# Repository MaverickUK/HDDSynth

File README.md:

# HDD Synth
<div style="background: white; display: inline-block; padding: 8px;">
  
</div>

### Recreates the sound of mechanical spinning HDDs on retro PCs that use a solid state drive.

Inspired by seeing the HDD Clicker project and wanting to more faithfully recreate the sound of old mechanical hard drives spinning up and accessing data. Because the hard drive sounds come from samples, it's possible to replace them with any hard drive recording you'd like or something completely different!

## Features

- **Sample based recreation** of mechanical hard disk drives operating sounds
 - **Spin up** when PC is turned on
 - **Idle hum** whilst standing by
 - **Access** clicks and crackcles
 - **Spin down** when PC is turned off
- **SD card** to hold multiple HDD sample packs, to recreate the sound of different mechanical hard disk drives
- **Volume control** to make it very loud or silent
- **Balance** to alter the amount of idle to access sounds
- **HDD detection** via HDD LED
- **HDD LED** to connect to your case
- **OLED screen** to view activity, volume and more

## Progress
### Beta test is active
The MKV prototype boards are with a small group of beta testers to shake out any last issues before the boards are made available for sale.

It's been a long road, but the end is in sight

## Media
[View gallery](media.md)

<!--
## Usage

## License
-->

## Contact
Peter Bridger at [maverickuk@gmail.com](maverickuk@gmail.com)

Project website at [www.strifestreams.com/hddsynth](https://www.strifestreams.com/hddsynth)

## Resources
- [ISA System Architecture by Tom Shanley](https://archive.org/details/ISA_System_Architecture)
- [Intel ISA Bus Specification](https://archive.org/details/bitsavers_intelbusSpep89_3342148)
- [ISA bus technical summary](http://wearcam.org/ece385/lecture6/isa.htm)

## Acknowledgments
- Inspired by the [HDD Clicker project](https://www.serdashop.com/HDDClicker)
- A big thanks to [Ian Scott of PicoGUS fame](https://picog.us/) for sharing his resource sources and knowledge of using the Pi Pico with the ISA bus which gave me the confidence to take this project to the next level
- [Marten Electric](https://www.martenelectric.cz/) for the excellent ISA prototyping boards which made it very easy to wire up the Pico to my computer

### PCBWay
Thanks to [PCBWay](https://www.pcbway.com) for their PCB manufacturing and assembly services. This is my first PCB based project and they've been a great way to get quality PCB prototypes created along with component assembly at competitive prices. Recommended if you're thinking about creating a simular project yourself.

## License
This project is dual-licensed:

- **Software/firmware** is licensed under the [GNU GPL v3.0](LICENSE-CODE).
- **Hardware designs** (schematics, PCB files, BOM) are licensed under
  [CC BY-NC-SA 4.0](LICENSE-HARDWARE) — free for personal, non-commercial
  use and modification, but commercial use requires my permission.

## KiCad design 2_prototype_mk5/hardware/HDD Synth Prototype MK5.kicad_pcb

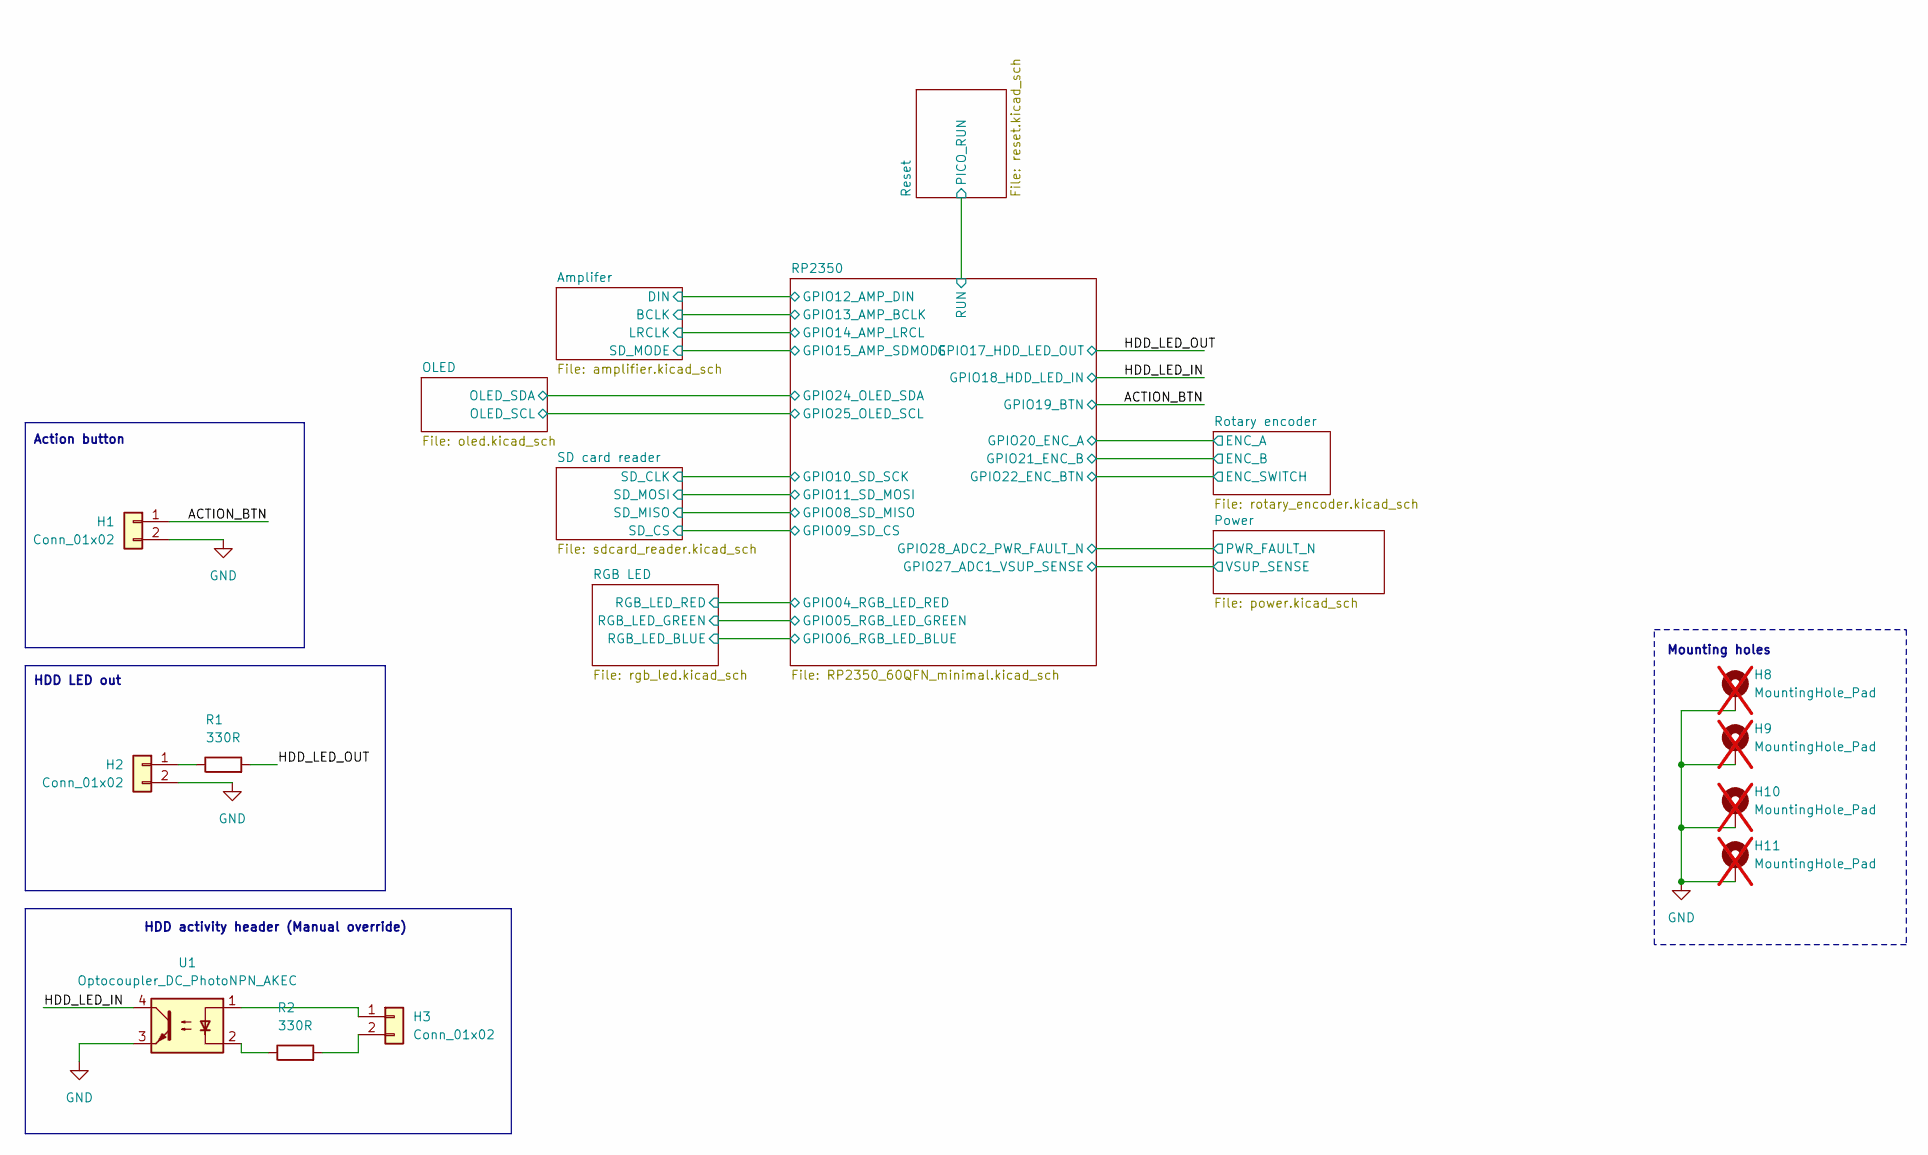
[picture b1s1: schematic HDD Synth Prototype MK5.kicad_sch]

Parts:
H1, H2, H3: Conn_01x02; PinHeader_1x02_P2.54mm_Vertical; LCSC Part Number C124375
H8, H9, H10, H11: MountingHole_Pad; MountingHole_3.2mm_M3_Pad; not fitted
R1, R2: 330R; R_0603_1608Metric; Manufacturer_Part_Number RC0603FR-07330RL; LCSC Part Number C23138
U1: Optocoupler_DC_PhotoNPN_AKEC; SO-4_4.4x3.6mm_P2.54mm; Manufacturer_Part_Number EL357N(C)(TA)-VG; LCSC Part Number C42381015

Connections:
/ACTION_BTN: H1.1; also elsewhere on the board
/HDD_LED_IN: U1.4; also elsewhere on the board
/HDD_LED_OUT: R1.2; also elsewhere on the board
GND: H1.2, H2.2, H8.1 (1_1), H9.1 (1_1), H10.1 (1_1), H11.1 (1_1), U1.3; also elsewhere on the board
unnamed: H2.1, R1.1
unnamed: H3.1, U1.1
unnamed: H3.2, R2.2
unnamed: R2.1, U1.2

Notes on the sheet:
Action button
Mounting holes
HDD activity header (Manual override)
HDD LED out

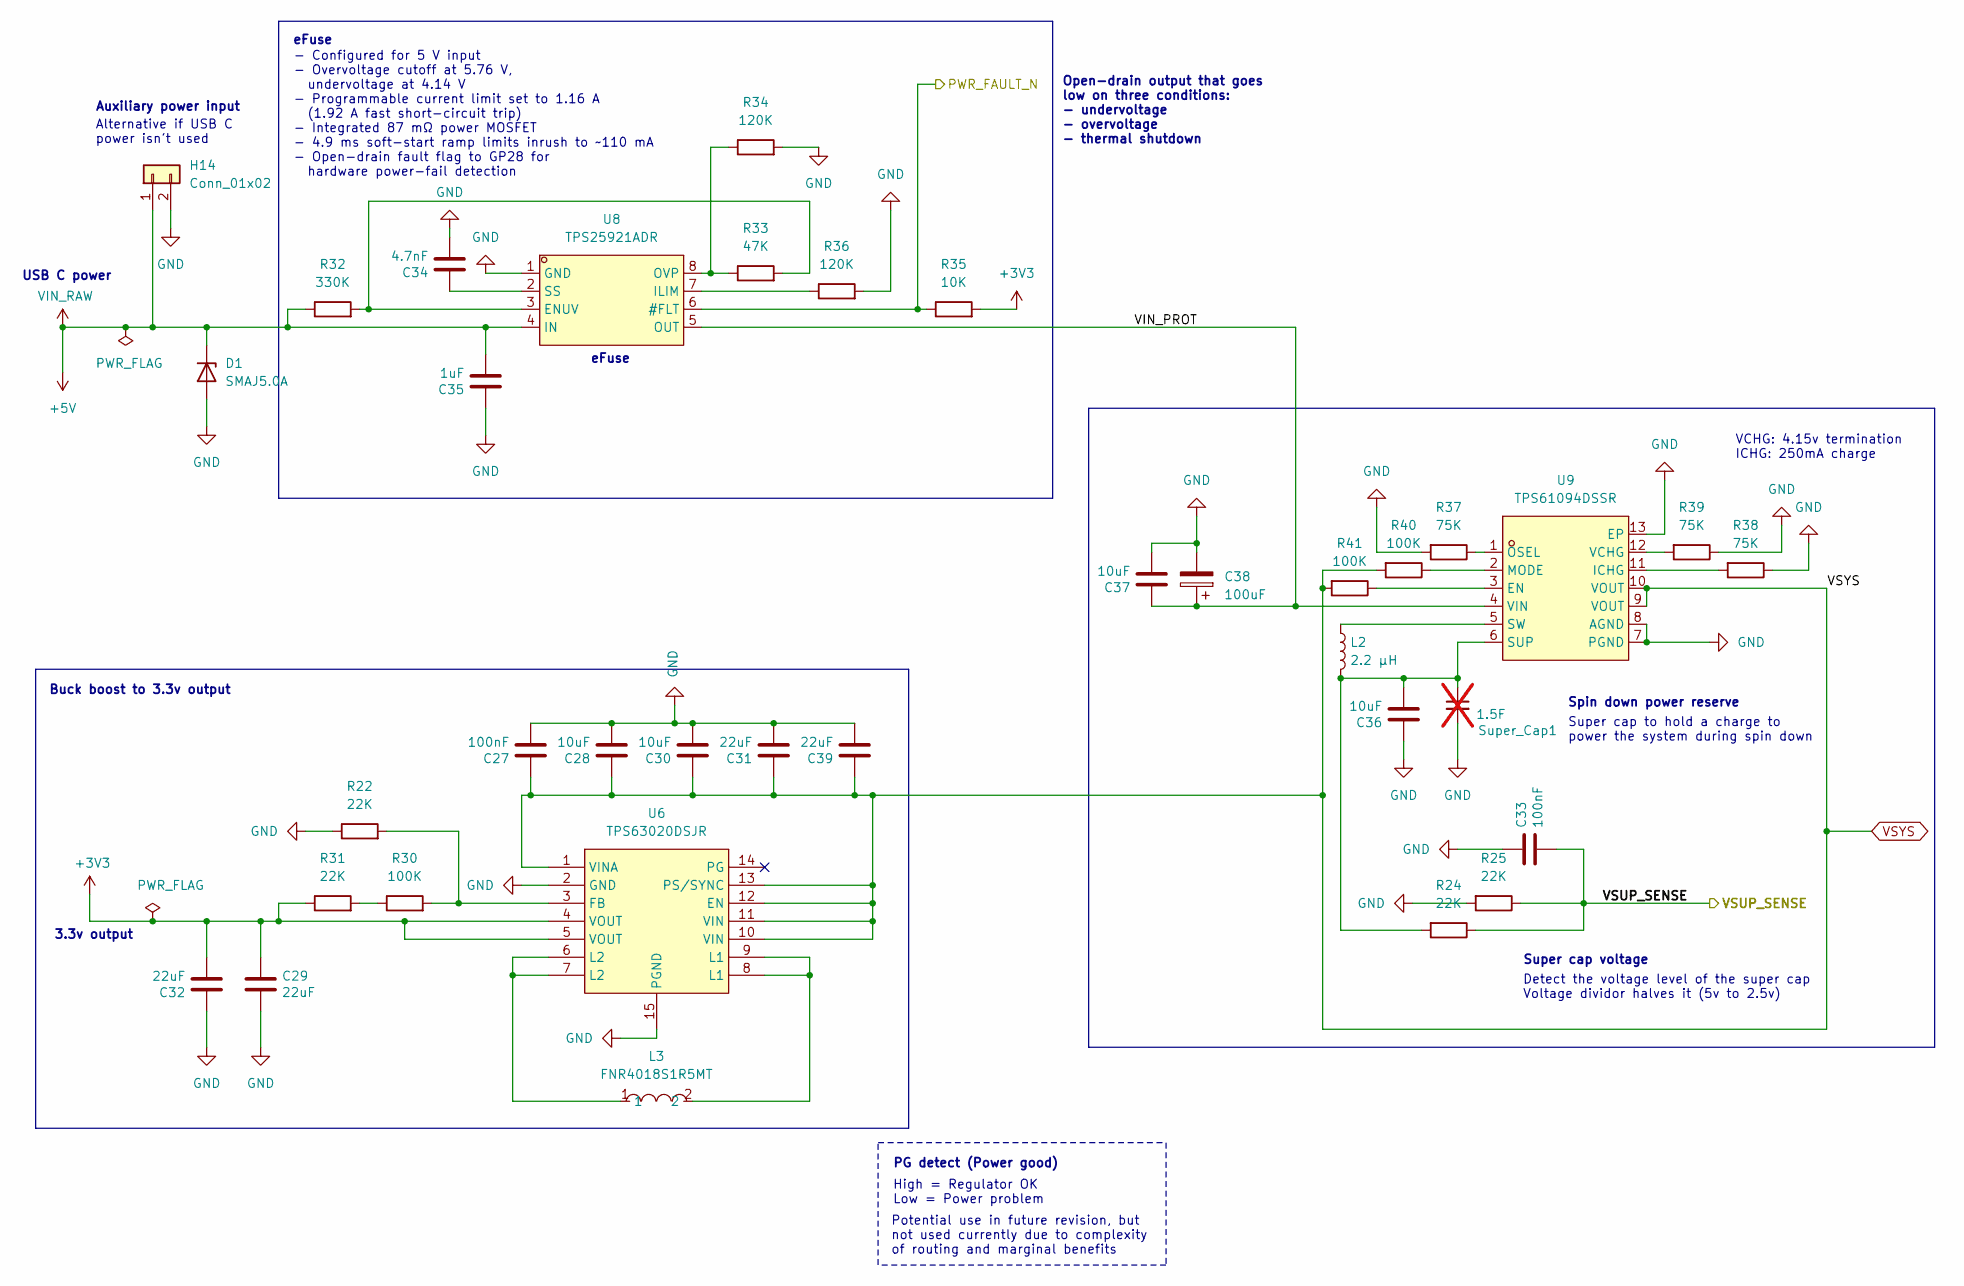
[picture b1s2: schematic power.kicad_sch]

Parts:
C27, C33: 100nF; C_0402_1005Metric; LCSC Part Number C1525
C28, C30, C36, C37: 10uF; C_0805_2012Metric; LCSC Part Number C15850
C29, C31, C32, C39: 22uF; C_0805_2012Metric; LCSC Part Number C45783
C34: 4.7nF; C_0402_1005Metric
C35: 1uF; C_0402_1005Metric
C38: 100uF; CP_Elec_6.3x7.7; LCSC Part Number C134801
D1: SMAJ5.0A; D_SMA
H14: Conn_01x02; PinHeader_1x02_P2.54mm_Vertical; LCSC Part Number C124375
L2: 2.2 µH; IND-SMD_L4.0-W4.0_FNR40XXS; LCSC Part Number C167804
L3: FNR4018S1R5MT; IND-SMD_L4.0-W4.0_FNR40XXS; MPN FNR4018S1R5MT; LCSC Part Number C167802
R22, R31: 22K; R_0402_1005Metric; LCSC Part Number C25768
R24, R25: 22K; R_0603_1608Metric; Manufacturer_Part_Number RC0603FR-071KL; LCSC Part Number C31850
R30, R40, R41: 100K; R_0402_1005Metric; LCSC Part Number C25741
R32: 330K; R_0402_1005Metric; LCSC Part Number C25778
R33: 47K; R_0402_1005Metric; LCSC Part Number C25792
R34, R36: 120K; R_0402_1005Metric; LCSC Part Number C25750
R35: 10K; R_0402_1005Metric; LCSC Part Number C25744
R37, R38, R39: 75K; R_0402_1005Metric; LCSC Part Number C25798
Super_Cap1: 1.5F; SuperCap_Eaton_PHV_9.0x17.3mm_P11.80mm; not fitted
U6: TPS63020DSJR; VSON-14_L4.0-W3.0-P0.50-BL-EP_TI_DSJ; MPN TPS63020DSJR; LCSC Part Number C15483
U8: TPS25921ADR; SOIC-8_L5.0-W4.0-P1.27-LS6.0-BL; MPN TPS25921ADR; LCSC Part Number C189199
U9: TPS61094DSSR; WSON-12_L3.0-W2.0-P0.5-BL-EP; MPN TPS61094DSSR; LCSC Part Number C3034939

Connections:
+3V3: C29.1, C32.2, R31.1, R35.2, U6.4 (VOUT), U6.5 (VOUT); also elsewhere on the board
+5V: C35.2, D1.1 (K), H14.1, R32.1, U8.4 (IN); also elsewhere on the board
/Power/VIN_PROT: C37.1, C38.1, U8.5 (OUT), U9.4 (VIN)
/Power/VSUP_SENSE: C33.2, R24.1, R25.1; also elsewhere on the board
/RP2350/PWR_FAULT_N: R35.1, U8.6 (#FLT); also elsewhere on the board
GND: C27.2, C28.2, C29.2, C30.2, C31.2, C32.1, C33.1, C34.2, C35.1, C36.1, C37.2, C38.2, C39.2, D1.2 (A), H14.2, R22.1, R25.2, R34.2, R36.2, R37.2, R38.1, R39.1, Super_Cap1.2, U6.2 (GND), U6.15 (PGND), U8.1 (GND), U9.7 (PGND), U9.8 (AGND), U9.13 (EP); also elsewhere on the board
unnamed: L3.1, U6.6 (L2), U6.7 (L2)
unnamed: L3.2, U6.8 (L1), U6.9 (L1)
unnamed: R30.1, R31.2
unnamed: R22.2, R30.2, U6.3 (FB)
unnamed: R32.2, R33.2, U8.3 (ENUV)
unnamed: R36.1, U8.7 (ILIM)
unnamed: R33.1, R34.1, U8.8 (OVP)
unnamed: C34.1, U8.2 (SS)
unnamed: R41.1, U9.3 (EN)
unnamed: R38.2, U9.11 (ICHG)
unnamed: R40.1, U9.2 (MODE)
unnamed: R37.1, U9.1 (OSEL)
unnamed: C36.2, L2.2, R24.2, Super_Cap1.1, U9.6 (SUP)
unnamed: L2.1, U9.5 (SW)
unnamed: R39.2, U9.12 (VCHG)
VSYS: C27.1, C28.1, C30.1, C31.1, C39.1, R40.2, R41.2, U6.1 (VINA), U6.10 (VIN), U6.11 (VIN), U6.12 (EN), U6.13 (PS/SYNC), U9.9 (VOUT), U9.10 (VOUT); also elsewhere on the board

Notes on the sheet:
Potential use in future revision, but not used currently due to complexity of routing and marginal benefits
- Configured for 5 V input - Overvoltage cutoff at 5.76 V, undervoltage at 4.14 V - Programmable current limit set to 1.16 A (1.92 A fast short-circuit trip) - Integrated 87 mΩ power MOSFET - 4.9 ms soft-start ramp limits inrush to ~110 mA - Open-drain fault flag to GP28 for hardware power-fail det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
Alternative if USB C power isn't used
VCHG: 4.15v termination ICHG: 250mA charge
Super cap to hold a charge to power the system during spin down
eFuse
3.3v output
Open-drain output that goes low on three conditions: - undervoltage - overvoltage - thermal shutdown
Super cap voltage
PG detect (Power good)
Buck boost to 3.3v output
Spin down power reserve
High = Regulator OK Low = Power problem
USB C power
Detect the voltage level of the super cap Voltage dividor halves it (5v to 2.5v)
Auxiliary power input

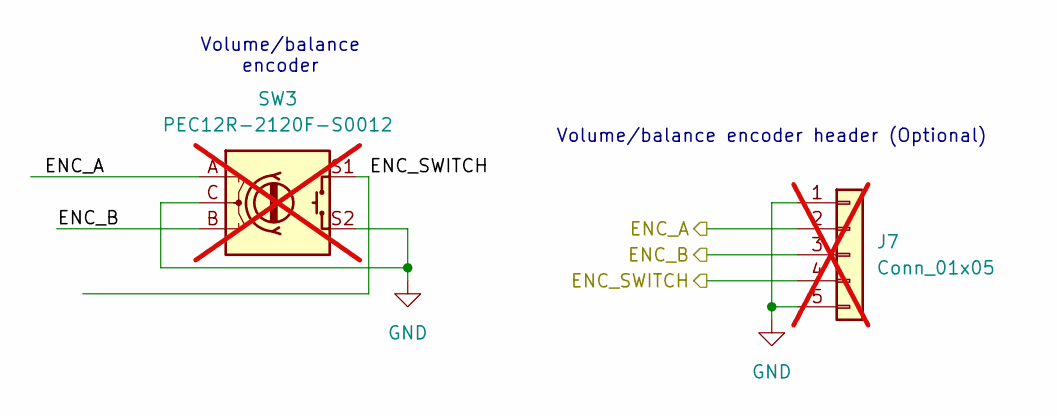
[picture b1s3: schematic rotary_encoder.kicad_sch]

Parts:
J7: Conn_01x05; PinHeader_1x05_P2.54mm_Vertical; LCSC Part Number C124379; not fitted
SW3: PEC12R-2120F-S0012; RotaryEncoder_Bourns_Horizontal_PEC12R-2x17F-Sxxxx; Manufacturer_Part_Number PEC12R-2120F-S0012; not fitted

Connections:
/RP2350/ENC_A: J7.2; also elsewhere on the board
/RP2350/ENC_B: J7.3; also elsewhere on the board
/RP2350/ENC_BTN: J7.4; also elsewhere on the board
GND: J7.1, J7.5, SW3.C, SW3.S2; also elsewhere on the board

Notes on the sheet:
Volume/balance encoder
Volume/balance encoder header (Optional)

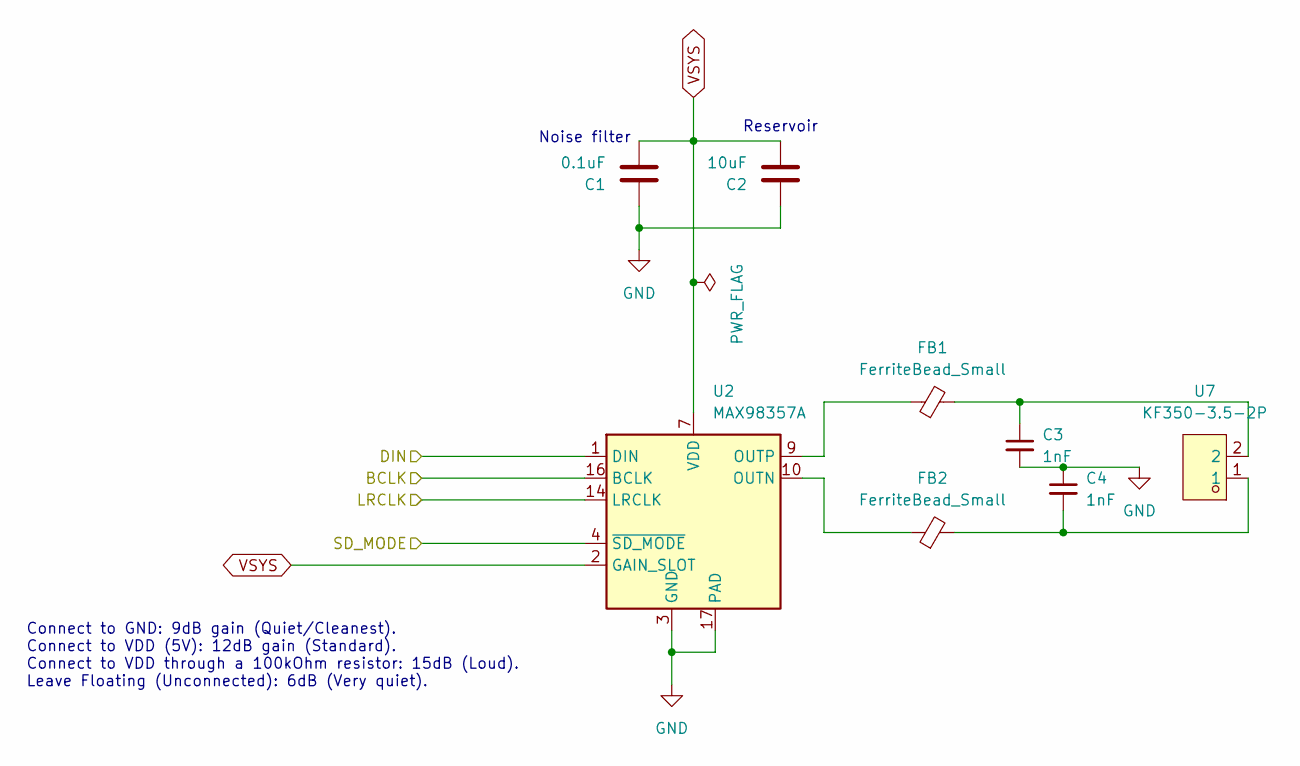
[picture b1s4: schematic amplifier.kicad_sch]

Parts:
C1: 0.1uF; C_0603_1608Metric; Manufacturer_Part_Number CL10B104KO8NNNC; LCSC Part Number C14663
C2: 10uF; C_1206_3216Metric; Manufacturer_Part_Number CL31A106KAHNNNE; LCSC Part Number C13585
C3, C4: 1nF; C_0603_1608Metric; Manufacturer_Part_Number 0603B102K500NT; LCSC Part Number C1588
FB1, FB2: FerriteBead_Small; L_0805_2012Metric; Manufacturer_Part_Number BLM21PG221SN1D; LCSC Part Number C85840
U2: MAX98357A; TQFN-16-1EP_3x3mm_P0.5mm_EP1.23x1.23mm; Manufacturer_Part_Number MAX98357AETE+T; LCSC Part Number C910544
U7: KF350-3.5-2P; CONN-TH_P3.50_KF350-3.5-2P; MPN KF350-3.5-2P; LCSC Part Number C474892

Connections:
/RP2350/AMP_BCLK: U2.16 (BCLK); also elsewhere on the board
/RP2350/AMP_DIN: U2.1 (DIN); also elsewhere on the board
/RP2350/AMP_LRCL: U2.14 (LRCLK); also elsewhere on the board
/RP2350/AMP_SDMODE: U2.4 (~SD_MODE); also elsewhere on the board
GND: C1.1, C2.1, C3.2, C4.1, U2.3 (GND), U2.11 (GND), U2.15 (GND), U2.17 (PAD); also elsewhere on the board
unnamed: C3.1, FB1.2, U7.2
unnamed: C4.2, FB2.2, U7.1
unnamed: FB2.1, U2.10 (OUTN)
unnamed: FB1.1, U2.9 (OUTP)
VSYS: C1.2, C2.2, U2.2 (GAIN_SLOT), U2.7 (VDD), U2.8 (VDD); also elsewhere on the board

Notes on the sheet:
Connect to GND: 9dB gain (Quiet/Cleanest). Connect to VDD (5V): 12dB gain (Standard). Connect to VDD through a 100kOhm resistor: 15dB (Loud). Leave Floating (Unconnected): 6dB (Very quiet).
Reservoir
Noise filter

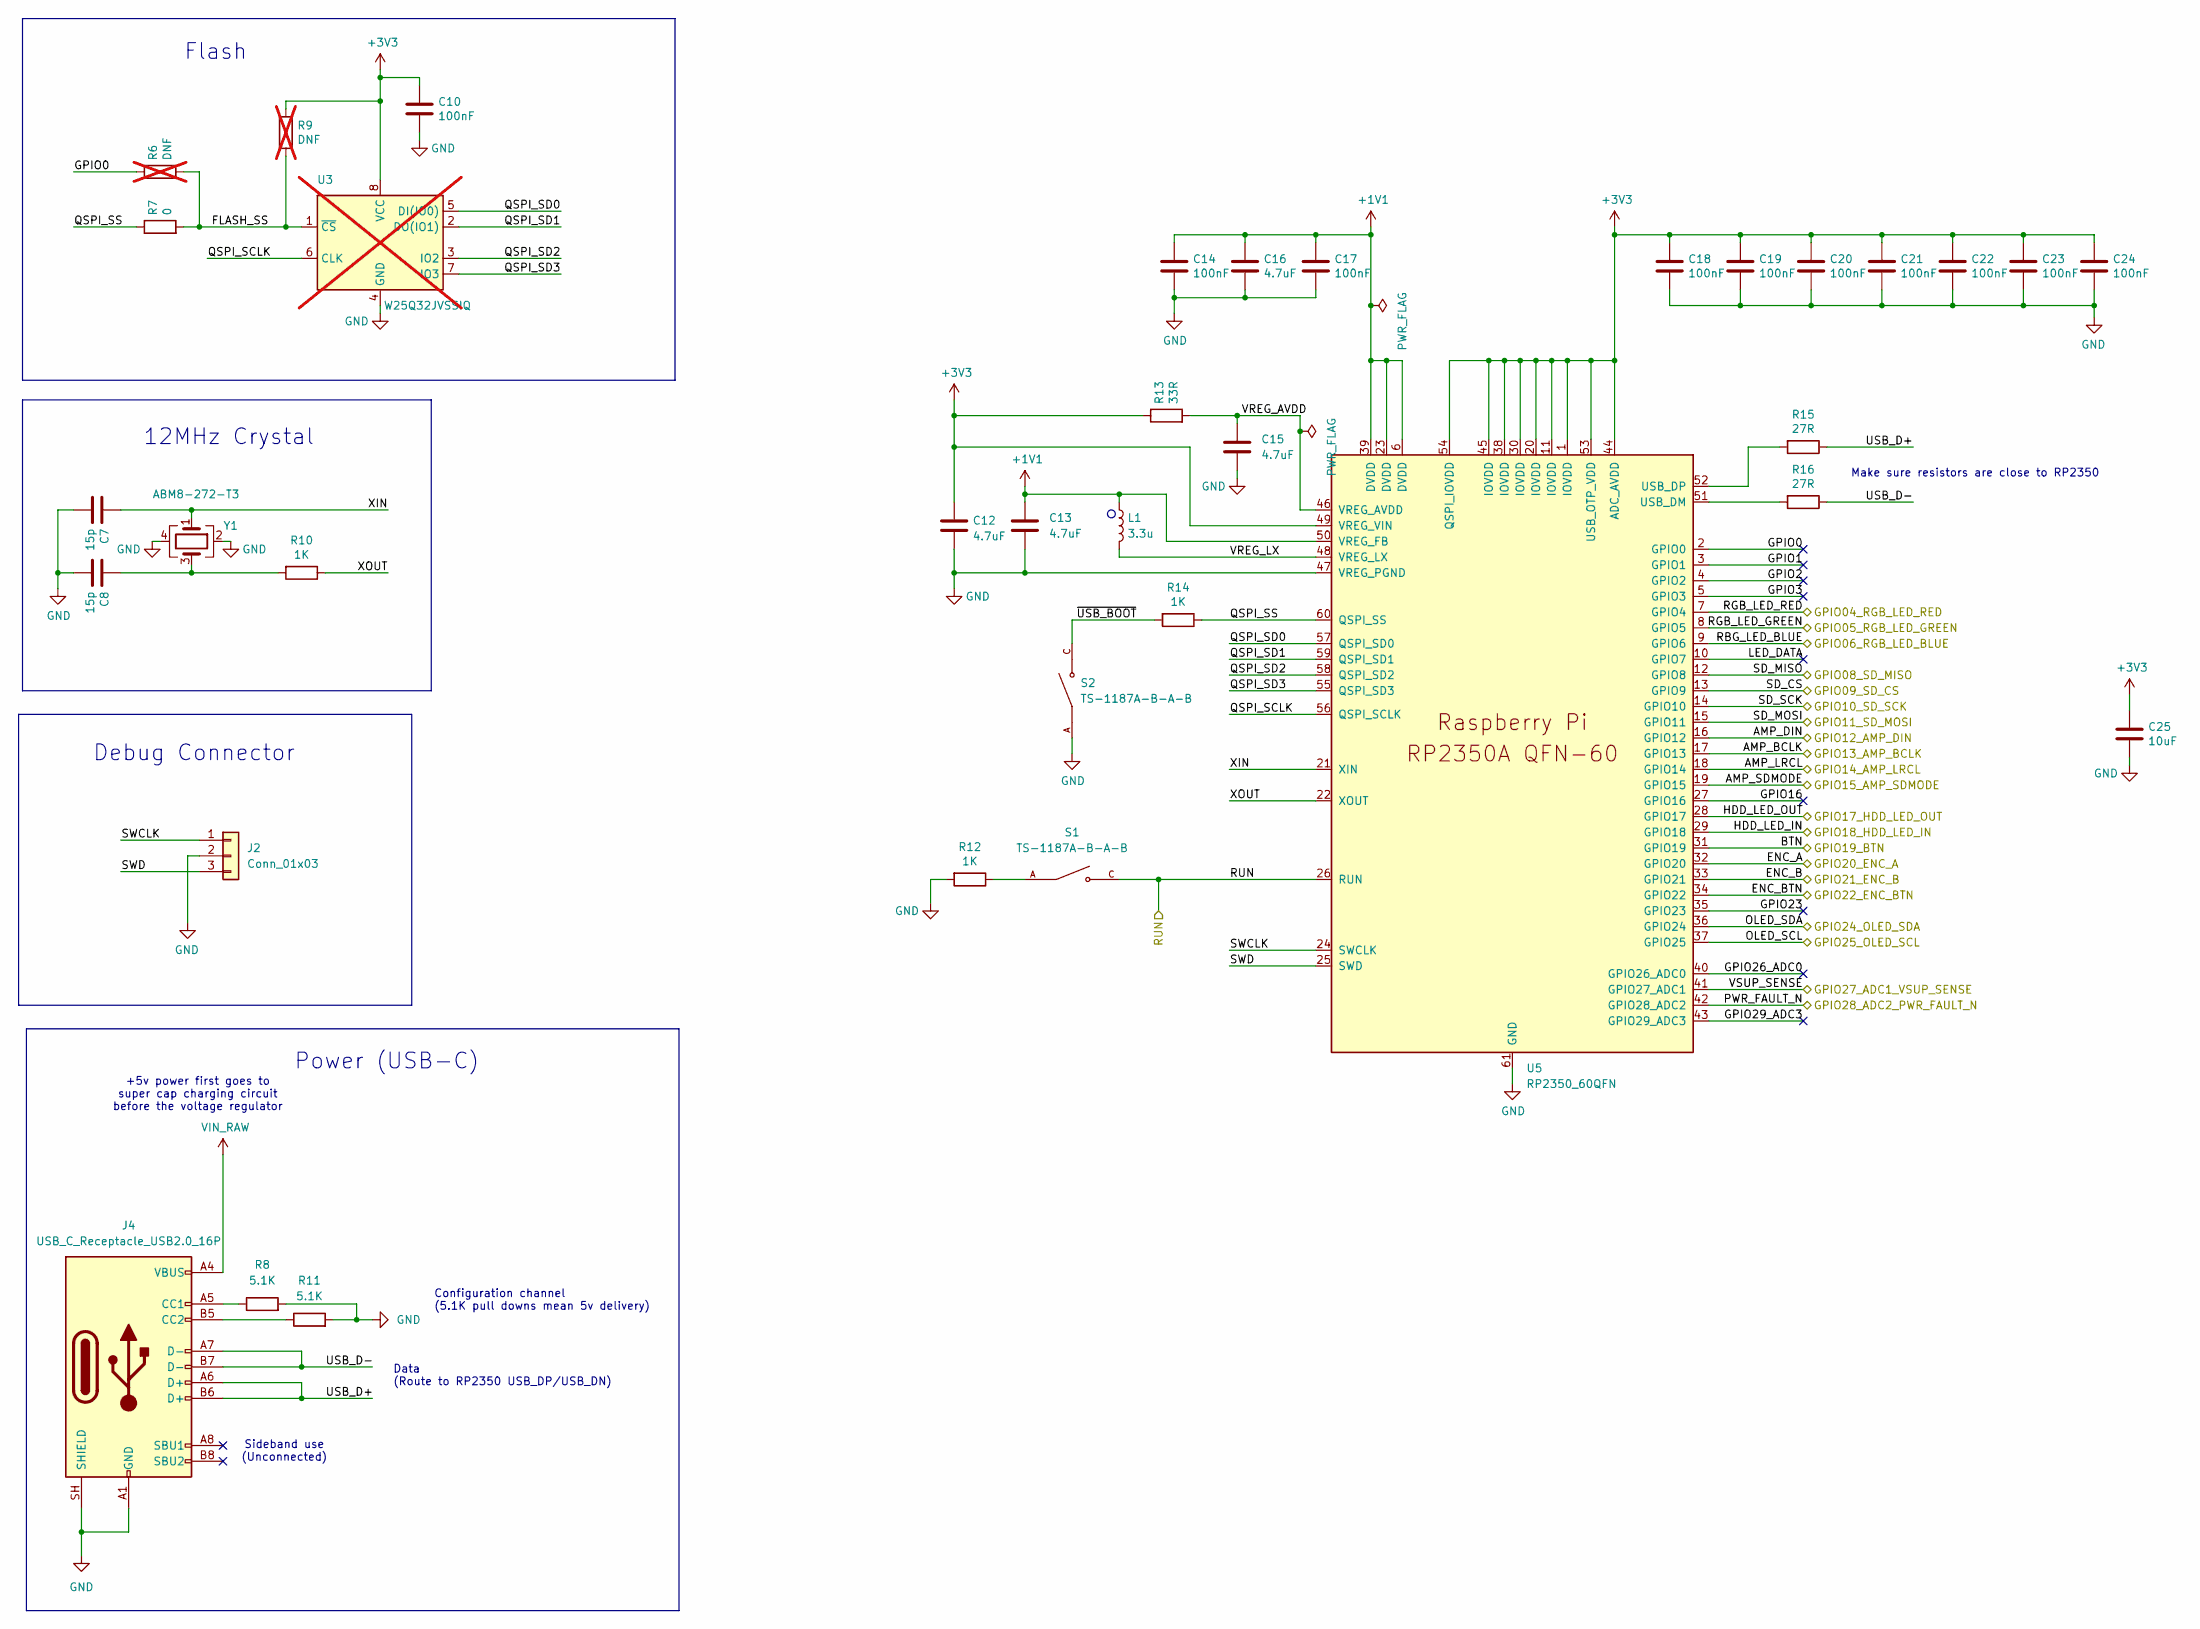
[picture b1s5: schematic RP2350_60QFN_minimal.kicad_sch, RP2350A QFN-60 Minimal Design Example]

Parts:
C7, C8: 15p; C_0402_1005Metric; LCSC Part Number C1548
C10, C14, C17, C18, C19, C20, C21, C22, C23, C24: 100nF; C_0402_1005Metric; LCSC Part Number C1525
C12, C13: 4.7uF; C_0402_1005Metric_small_pads; LCSC Part Number C23733
C15, C16: 4.7uF; C_0402_1005Metric; LCSC Part Number C23733
C25: 10uF; C_0805_2012Metric; LCSC Part Number C15850
J2: Conn_01x03; PinHeader_1x03_P2.54mm_Vertical; LCSC Part Number C49257
J4: USB_C_Receptacle_USB2.0_16P; USB_C_Receptacle_HRO_TYPE-C-31-M-12; LCSC Part Number C165948
L1: 3.3u; L_pol_2016; LCSC Part Number C42411119
R6, R9: DNF; R_0402_1005Metric; not fitted
R7: 0; R_0402_1005Metric; LCSC Part Number C17168
R8, R11: 5.1K; R_0402_1005Metric; LCSC Part Number C25905
R10, R12, R14: 1K; R_0402_1005Metric; LCSC Part Number C11702
R13: 33R; R_0402_1005Metric; LCSC Part Number C25105
R15, R16: 27R; R_0402_1005Metric; LCSC Part Number C25100
S1, S2: TS-1187A-B-A-B; SW_TS-1187A-B-A-B; PARTREV A0; LCSC Part Number C318884
U3: W25Q32JVSSIQ; SOIC-8_5.23x5.23mm_P1.27mm; LCSC Part Number C179173; not fitted
U5: RP2350_60QFN; RP2350-QFN-60-1EP_7x7_P0.4mm_EP3.4x3.4mm_ThermalVias; LCSC Part Number C41378174
Y1: ABM8-272-T3; Crystal_SMD_3225-4Pin_3.2x2.5mm; LCSC Part Number C20617575

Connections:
+1V1: C13.1, C14.1, C16.1, C17.1, L1.1, U5.6 (DVDD), U5.23 (DVDD), U5.39 (DVDD), U5.50 (VREG_FB)
+3V3: C10.1, C12.1, C18.1, C19.1, C20.1, C21.1, C22.1, C23.1, C24.1, C25.1, R9.1, R13.1, U3.8 (VCC), U5.1 (IOVDD), U5.11 (IOVDD), U5.20 (IOVDD), U5.30 (IOVDD), U5.38 (IOVDD), U5.44 (ADC_AVDD), U5.45 (IOVDD), U5.49 (VREG_VIN), U5.53 (USB_OTP_VDD), U5.54 (QSPI_IOVDD); also elsewhere on the board
+5V: J4.A4 (VBUS), J4.A9 (VBUS), J4.B4 (VBUS), J4.B9 (VBUS); also elsewhere on the board
/ACTION_BTN: U5.31 (GPIO19); also elsewhere on the board
/HDD_LED_IN: U5.29 (GPIO18); also elsewhere on the board
/HDD_LED_OUT: U5.28 (GPIO17); also elsewhere on the board
/Power/VSUP_SENSE: U5.41 (GPIO27_ADC1); also elsewhere on the board
/RP2350/AMP_BCLK: U5.17 (GPIO13); also elsewhere on the board
/RP2350/AMP_DIN: U5.16 (GPIO12); also elsewhere on the board
/RP2350/AMP_LRCL: U5.18 (GPIO14); also elsewhere on the board
/RP2350/AMP_SDMODE: U5.19 (GPIO15); also elsewhere on the board
/RP2350/ENC_A: U5.32 (GPIO20); also elsewhere on the board
/RP2350/ENC_B: U5.33 (GPIO21); also elsewhere on the board
/RP2350/ENC_BTN: U5.34 (GPIO22); also elsewhere on the board
/RP2350/FLASH_SS: R6.2, R7.2, R9.2, U3.1 (~CS)
/RP2350/GPIO0: R6.1, U5.2 (GPIO0)
/RP2350/GPIO1: U5.3 (GPIO1)
/RP2350/GPIO2: U5.4 (GPIO2)
/RP2350/GPIO3: U5.5 (GPIO3)
/RP2350/GPIO16: U5.27 (GPIO16)
/RP2350/GPIO23: U5.35 (GPIO23)
/RP2350/GPIO26_ADC0: U5.40 (GPIO26_ADC0)
/RP2350/GPIO29_ADC3: U5.43 (GPIO29_ADC3)
/RP2350/LED_DATA: U5.10 (GPIO7)
/RP2350/OLED_SCL: U5.37 (GPIO25); also elsewhere on the board
/RP2350/OLED_SDA: U5.36 (GPIO24); also elsewhere on the board
/RP2350/PWR_FAULT_N: U5.42 (GPIO28_ADC2); also elsewhere on the board
/RP2350/QSPI_SCLK: U3.6 (CLK), U5.56 (QSPI_SCLK)
/RP2350/QSPI_SD0: U3.5 (DI(IO0)), U5.57 (QSPI_SD0)
/RP2350/QSPI_SD1: U3.2 (DO(IO1)), U5.59 (QSPI_SD1)
/RP2350/QSPI_SD2: U3.3 (IO2), U5.58 (QSPI_SD2)
/RP2350/QSPI_SD3: U3.7 (IO3), U5.55 (QSPI_SD3)
/RP2350/QSPI_SS: R7.1, R14.1, U5.60 (QSPI_SS)
/RP2350/RBG_LED_BLUE: U5.9 (GPIO6); also elsewhere on the board
/RP2350/RGB_LED_GREEN: U5.8 (GPIO5); also elsewhere on the board
/RP2350/RGB_LED_RED: U5.7 (GPIO4); also elsewhere on the board
/RP2350/RUN: S1.C, S1.D, U5.26 (RUN); also elsewhere on the board
/RP2350/SD_CS: U5.13 (GPIO9); also elsewhere on the board
/RP2350/SD_MISO: U5.12 (GPIO8); also elsewhere on the board
/RP2350/SD_MOSI: U5.15 (GPIO11); also elsewhere on the board
/RP2350/SD_SCK: U5.14 (GPIO10); also elsewhere on the board
/RP2350/SWCLK: J2.1, U5.24 (SWCLK)
/RP2350/SWD: J2.3, U5.25 (SWD)
/RP2350/USB_D+: J4.A6 (D+), J4.B6 (D+), R15.1
/RP2350/USB_D-: J4.A7 (D-), J4.B7 (D-), R16.1
/RP2350/VREG_AVDD: C15.1, R13.2, U5.46 (VREG_AVDD)
/RP2350/VREG_LX: L1.2, U5.48 (VREG_LX)
/RP2350/XIN: C7.1, U5.21 (XIN), Y1.1
/RP2350/XOUT: R10.1, U5.22 (XOUT)
/RP2350/~USB_BOOT: R14.2, S2.C, S2.D
GND: C7.2, C8.2, C10.2, C12.2, C13.2, C14.2, C15.2, C16.2, C17.2, C18.2, C19.2, C20.2, C21.2, C22.2, C23.2, C24.2, C25.2, J2.2, J4.A1 (GND), J4.A12 (GND), J4.B1 (GND), J4.B12 (GND), J4.SH (SHIELD), R8.2, R11.2, R12.2, S2.A, S2.B, U3.4 (GND), U5.47 (VREG_PGND), U5.61 (GND), Y1.2, Y1.4; also elsewhere on the board
unnamed: C8.1, R10.2, Y1.3
unnamed: J4.A5 (CC1), R8.1
unnamed: J4.B5 (CC2), R11.1
unnamed: R12.1, S1.A, S1.B
unnamed: R16.2, U5.51 (USB_DM)
unnamed: R15.2, U5.52 (USB_DP)

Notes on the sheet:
+5v power first goes to super cap charging circuit before the voltage regulator
Debug Connector
Configuration channel (5.1K pull downs mean 5v delivery)
Flash
Data (Route to RP2350 USB_DP/USB_DN)
Make sure resistors are close to RP2350
12MHz Crystal
Power (USB-C)
Sideband use (Unconnected)

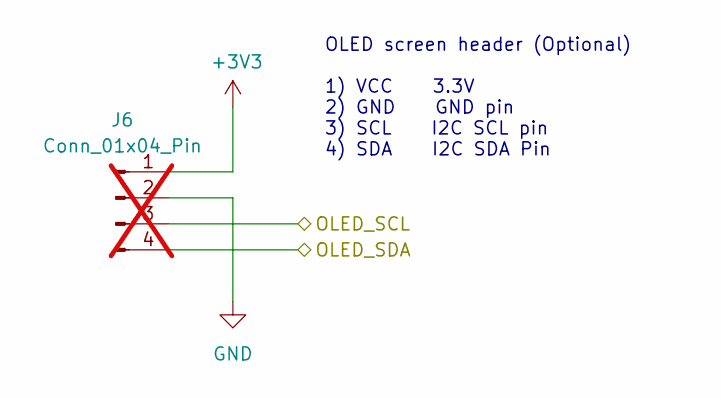
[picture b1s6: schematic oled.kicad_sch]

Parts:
J6: Conn_01x04_Pin; PinHeader_1x04_P2.54mm_Vertical; LCSC Part Number C124378; not fitted

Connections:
+3V3: J6.1; also elsewhere on the board
/RP2350/OLED_SCL: J6.3; also elsewhere on the board
/RP2350/OLED_SDA: J6.4; also elsewhere on the board
GND: J6.2; also elsewhere on the board

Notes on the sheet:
OLED screen header (Optional) 1) VCC 3.3V 2) GND GND pin 3) SCL I2C SCL pin 4) SDA I2C SDA Pin

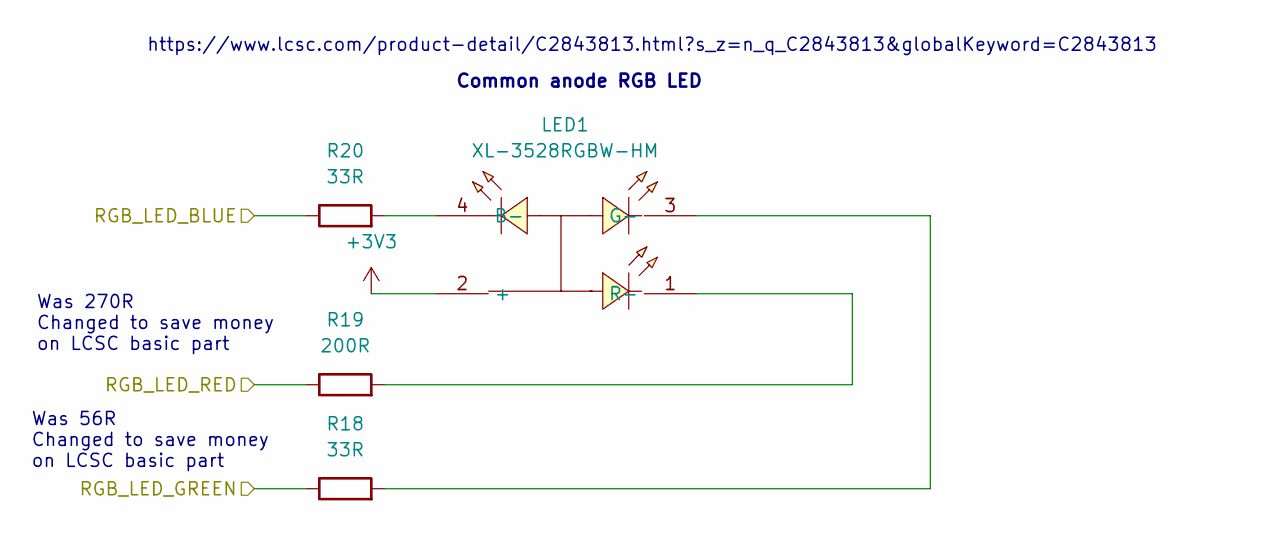
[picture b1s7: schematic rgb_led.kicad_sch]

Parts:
LED1: XL-3528RGBW-HM; LED-SMD_4P-L3.2-W2.8-LS3.5-XL-3528RGBW-HM5; MPN XL-3528RGBW-HM; LCSC Part Number C2843813
R18, R20: 33R; R_0402_1005Metric; LCSC Part Number C25105
R19: 200R; R_0402_1005Metric; LCSC Part Number C25087

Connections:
+3V3: LED1.2 (+); also elsewhere on the board
/RP2350/RBG_LED_BLUE: R20.1; also elsewhere on the board
/RP2350/RGB_LED_GREEN: R18.1; also elsewhere on the board
/RP2350/RGB_LED_RED: R19.1; also elsewhere on the board
unnamed: LED1.4 (B-), R20.2
unnamed: LED1.3 (G-), R18.2
unnamed: LED1.1 (R-), R19.2

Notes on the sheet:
Was 270R Changed to save money on LCSC basic part
https://www.lcsc.com/product-detail/C2843813.html?s_z=n_q_C2843813&globalKeyword=C2843813
Common anode RGB LED
Was 56R Changed to save money on LCSC basic part

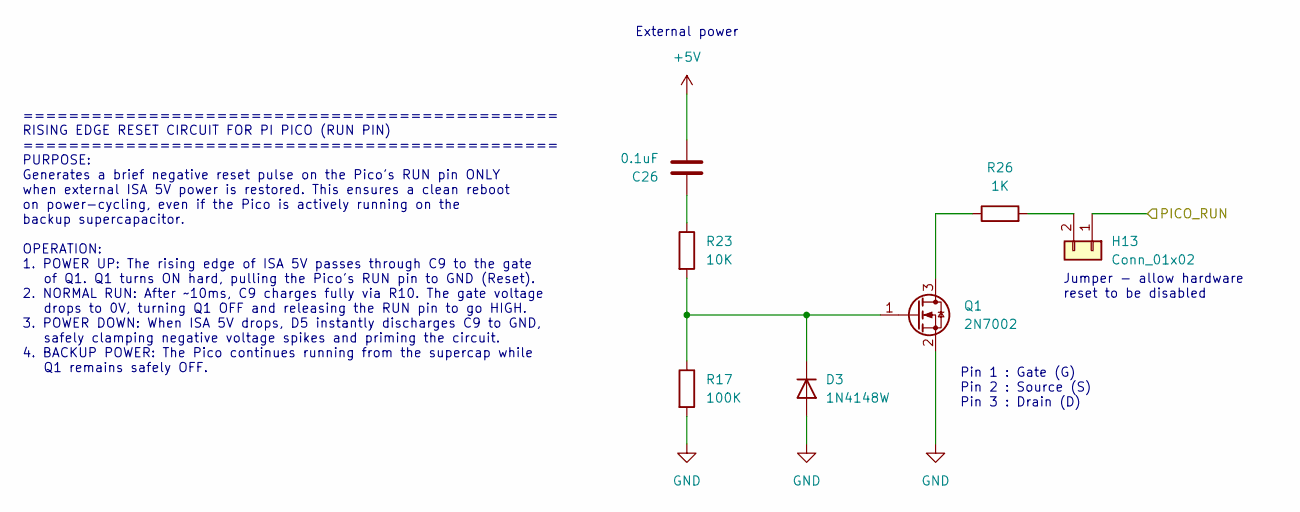
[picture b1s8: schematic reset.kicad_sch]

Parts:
C26: 0.1uF; C_0603_1608Metric; Manufacturer_Part_Number CL10B104KO8NNNC; LCSC Part Number C14663
D3: 1N4148W; D_SOD-123; LCSC Part Number C81598
H13: Conn_01x02; PinHeader_1x02_P2.54mm_Vertical; LCSC Part Number C124375
Q1: 2N7002; SOT-23; LCSC Part Number C8545
R17: 100K; R_0402_1005Metric; LCSC Part Number C25741
R23: 10K; R_0402_1005Metric; LCSC Part Number C25744
R26: 1K; R_0402_1005Metric; LCSC Part Number C11702

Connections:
+5V: C26.2; also elsewhere on the board
/RP2350/RUN: H13.1; also elsewhere on the board
GND: D3.2 (A), Q1.2 (S), R17.2; also elsewhere on the board
unnamed: C26.1, R23.1
unnamed: D3.1 (K), Q1.1 (G), R17.1, R23.2
unnamed: H13.2, R26.2
unnamed: Q1.3 (D), R26.1

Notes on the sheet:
Jumper - allow hardware reset to be disabled
=============================================== RISING EDGE RESET CIRCUIT FOR PI PICO (RUN PIN) =============================================== PURPOSE: Generates a brief negative reset pulse on the Pico's RUN pin ONLY when external ISA 5V power is restored. This ensures a clean reboot on power-cyc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
Pin 1 : Gate (G) Pin 2 : Source (S) Pin 3 : Drain (D)
External power

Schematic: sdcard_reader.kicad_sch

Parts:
C5: 10uF; C_1206_3216Metric; Manufacturer_Part_Number CL31A106KAHNNNE; LCSC Part Number C13585
C6: 0.1uF; C_0603_1608Metric; Manufacturer_Part_Number CL10B104KO8NNNC; LCSC Part Number C14663
Card1: TF-015; TF-SMD_TF-015; MPN TF-015; LCSC Part Number C113206
R27, R28, R29: 47K; R_0402_1005Metric; LCSC Part Number C25792

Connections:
+3V3: C5.1, C6.1, Card1.4 (VDD), R27.1, R28.1, R29.1; also elsewhere on the board
/RP2350/SD_CS: Card1.2 (CDDAT3(CS)), R28.2; also elsewhere on the board
/RP2350/SD_MISO: Card1.7 (DAT0(D0)), R27.2; also elsewhere on the board
/RP2350/SD_MOSI: Card1.3 (CMD(DI)), R29.2; also elsewhere on the board
/RP2350/SD_SCK: Card1.5 (CLK(SCLK)); also elsewhere on the board
GND: C5.2, C6.2, Card1.6 (VSS), Card1.10 (GND), Card1.11 (GND), Card1.12 (GND), Card1.13 (GND); also elsewhere on the board

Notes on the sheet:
Stops ERC error
Master In, Slave Out
Pull ups
Filter
Chip select
Master out, Slave in
Reservour
Serial clock
